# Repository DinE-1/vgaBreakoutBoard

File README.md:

# VGA Breakout

A KiCad PCB breakout board providing easy access to VGA connector pins.

# Pictures

## Front

## Front with components

## Back

## License

Copyright (c) 2026 DinE-1

Licensed under the CERN Open Hardware Licence Version 2 - Permissive (CERN-OHL-P v2).

See the LICENSE file for details.

## Disclaimer

This design is provided as-is, without warranty of any kind.

Verify electrical compatibility and suitability for your application before manufacture or use. DinE-1 assumes no responsibility for damage, malfunction, data loss, or other consequences resulting from use of this design.

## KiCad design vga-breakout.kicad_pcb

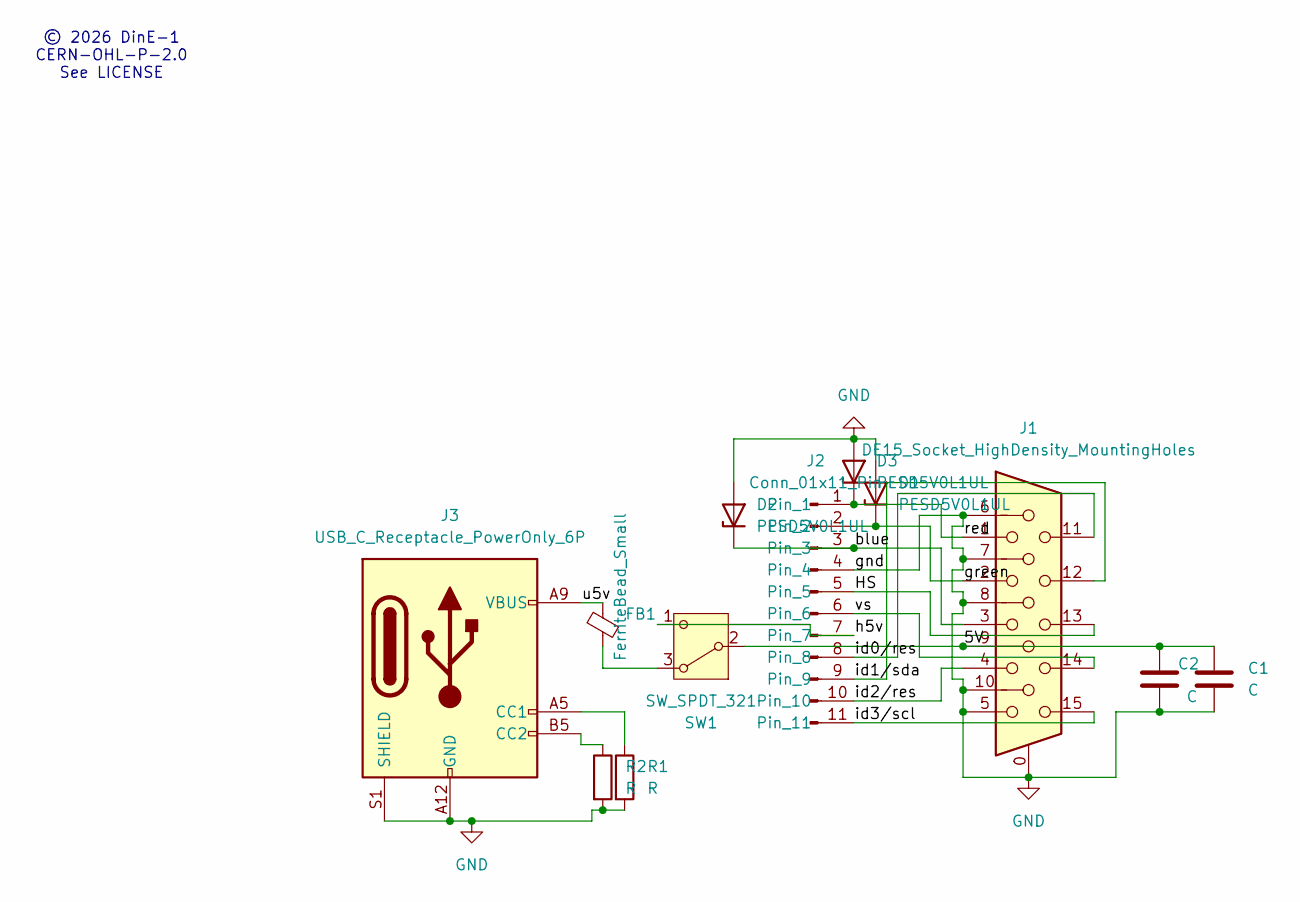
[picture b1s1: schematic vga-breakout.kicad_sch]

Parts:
C1, C2: C; C_0603_1608Metric
D1, D2, D3: PESD5V0L1UL; D_SOD-882
FB1: FerriteBead_Small; L_0805_2012Metric
J1: DE15_Socket_HighDensity_MountingHoles; DSUB-15-HD_Socket_Vertical_P2.29x1.98mm_MountingHoles
J2: Conn_01x11_Pin; PinHeader_1x11_P2.54mm_Vertical
J3: USB_C_Receptacle_PowerOnly_6P; USB_C_Receptacle_GCT_USB4125-xx-x_6P_TopMnt_Horizontal
R1, R2: R; R_0603_1608Metric
SW1: SW_SPDT_321; SW_SPDT_PCM12

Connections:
/5V: C1.1, C2.1, J1.9, SW1.2 (B)
/HS: J1.13, J2.5
/blue: D2.1 (K), J1.3, J2.3
/green: D1.1 (K), J1.2, J2.2
/h5v: J2.7, SW1.1 (C)
/id0/res: J1.11, J2.8
/id1/sda: J1.12, J2.9
/id2/res: J1.4, J2.10
/id3/scl: J1.15, J2.11
/red: D3.1 (K), J1.1, J2.1
/u5v: FB1.2, J3.A9 (VBUS), J3.B9 (VBUS)
/vs: J1.14, J2.6
GND: C1.2, C2.2, D1.2 (A), D2.2 (A), D3.2 (A), J1.0, J1.5, J1.6, J1.7, J1.8, J1.10, J2.4, J3.A12 (GND), J3.B12 (GND), J3.S1 (SHIELD), R1.2, R2.2
unnamed: J3.A5 (CC1), R1.1
unnamed: J3.B5 (CC2), R2.1
unnamed: FB1.1, SW1.3 (A)

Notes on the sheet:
© 2026 DinE-1 CERN-OHL-P-2.0 See LICENSE

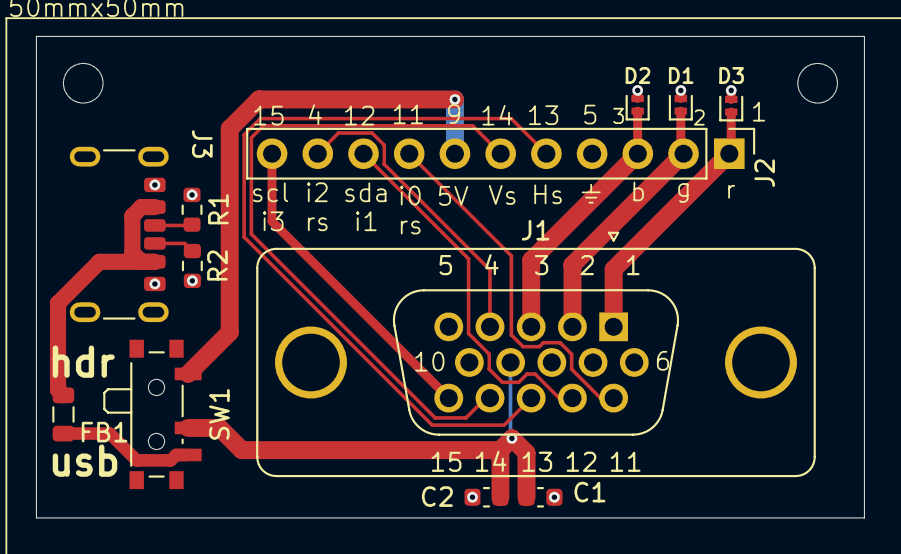
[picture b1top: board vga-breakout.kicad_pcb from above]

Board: 2 copper layers, 46.0 x 26.8 mm, 12 parts (0 on the bottom side), 16 nets.

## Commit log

2026-05-30 Initial VGA breakout board design
2026-05-30 organise export
2026-05-30 add pics
2026-05-30 remove ferrite from sheilding, rerouting
2026-05-30 less angled
2026-05-31 add tvs diode, reroute
    reroute with vias only for 5V trace
2026-06-19 silkscreen
    moving text
